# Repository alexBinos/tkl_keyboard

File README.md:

# tkl_keyboard

A custom tenkeyless keyboard with extra hardware features including;

- ATMEGA32U4 microcontroller compatible with QMK firmware
- 2x optional rotary encoders
- I2C breakout to support an OLED display
- Per-key RGB LED lighting and underglow lighting
- Hot-swap key switch sockets
- 4 port USB 2.0 HUB with 3 spare downstream ports
- Optional external power circuit supplying up to 2A for USB downstream and onboard power requirements

<br>

See `Firmware/` for example QMK projects. Note that some pin assignments changed between v0 and v1, see `Documents/tkl_keyboard v1 changes.md`. Pre-built binaries for the default configurations are also provided in `Firmware/bin`.

<br>

There are two versions of the case, both are compatible with hardware v0 and v1. The v1 case is a more integrated design, easier to assemble and can be positioned at a number of different angles.

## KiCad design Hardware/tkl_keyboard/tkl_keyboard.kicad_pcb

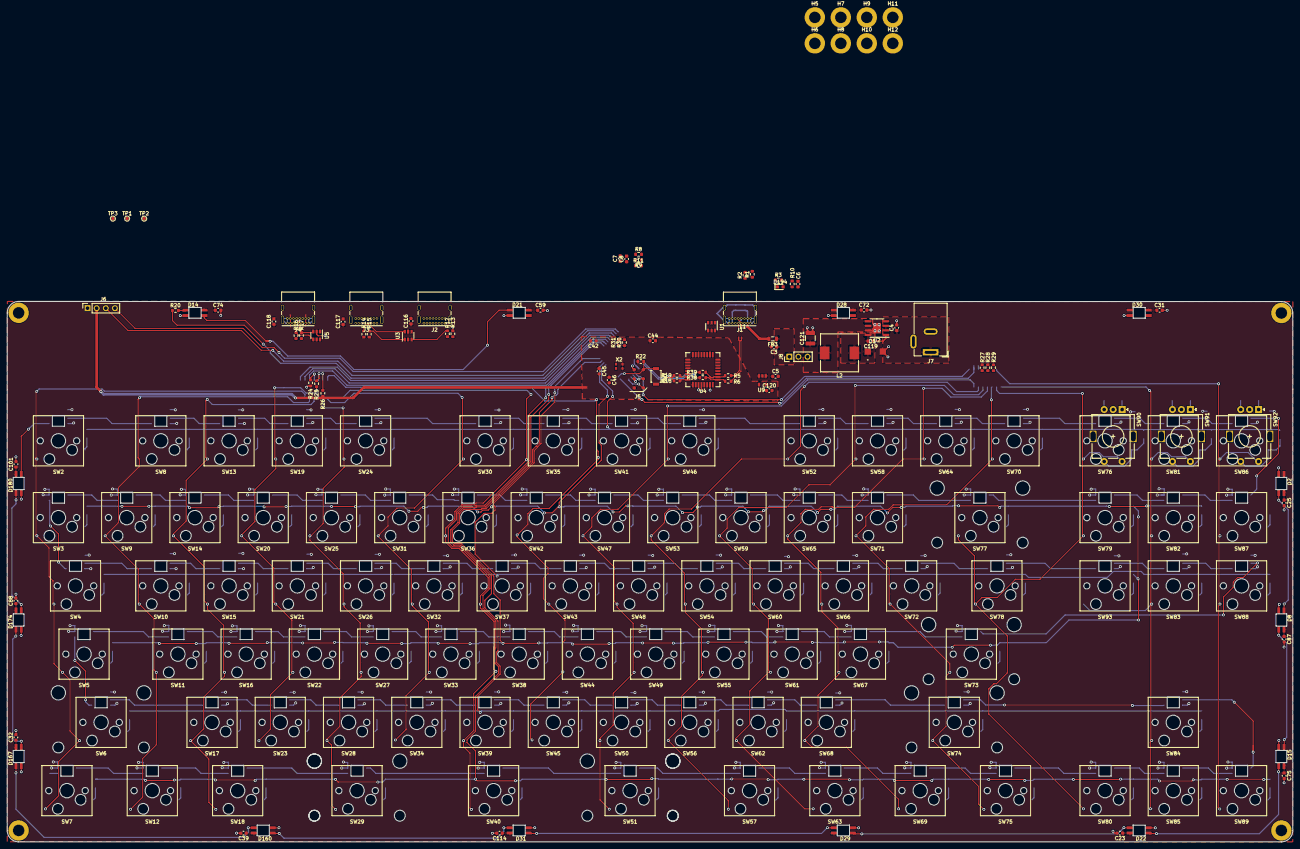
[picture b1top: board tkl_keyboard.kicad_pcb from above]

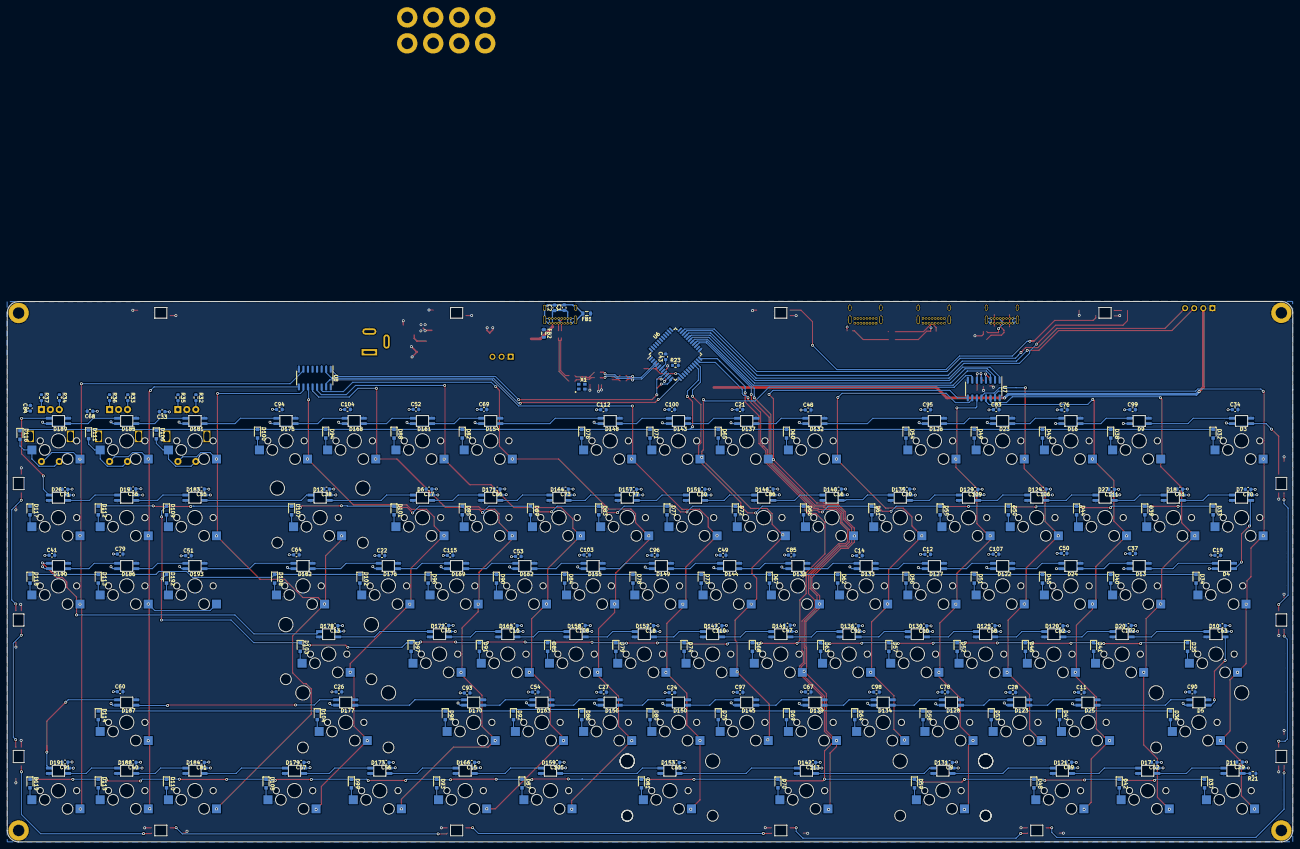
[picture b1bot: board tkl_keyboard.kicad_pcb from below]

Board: 2 copper layers, 358.8 x 150.8 mm, 484 parts (209 on the bottom side), 283 nets.

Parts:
C1, C4: 10uF; C_0603_1608Metric
C2, C6, C7, C43, C46, C116, C117, C118, C120: 1uF; C_0603_1608Metric
C3, C5, C8, C9, C10, C11, C12, C13, C14, C15, C16, C17, C18, C19, C20, C21, C22, C23, C24, C25, C26, C27, C28, C29, C30, C31, C32, C33, C34, C35, C36, C37, C38, C39, C40, C41, C42, C44, C45, C47, C48, C49, C50, C51, C52, C53, C54, C55, C56, C57, C58, C59, C60, C61, C62, C63, C64, C65, C66, C67, C68, C69, C70, C71, C72, C73, C74, C75, C76, C77, C78, C79, C80, C81, C82, C83, C84, C85, C86, C87, C88, C89, C90, C91, C92, C93, C94, C95, C96, C97, C98, C99, C100, C101, C102, C103, C104, C105, C106, C107, C108, C109, C110, C111, C112, C113, C114, C115, C119: 100nF; C_0603_1608Metric
C121: 47uF; C_1210_3225Metric
D1: D; DO-214AC
D2: UG_4; SK6812-MINI-E
D3: K0; SK6812-MINI-E
D4: K32; SK6812-MINI-E
D5: K63; SK6812-MINI-E
D6: K28; SK6812-MINI-E
D7: K16; SK6812-MINI-E
D8: UG_5; SK6812-MINI-E
D9: K1; SK6812-MINI-E
D10: K48; SK6812-MINI-E
D11: K77; SK6812-MINI-E
D12: K29; SK6812-MINI-E
D13: K33; SK6812-MINI-E
D14: UG_0; SK6812-MINI-E
D15: UG_6; SK6812-MINI-E
D16: K2; SK6812-MINI-E
D17: K64; SK6812-MINI-E
D18: K17; SK6812-MINI-E
D19: K30; SK6812-MINI-E
D20: K49; SK6812-MINI-E
D21: UG_1; SK6812-MINI-E
D22: UG_7; SK6812-MINI-E
D23: K3; SK6812-MINI-E
D24: K34; SK6812-MINI-E
D25: K65; SK6812-MINI-E
D26: K31; SK6812-MINI-E
D27: K18; SK6812-MINI-E
D28: UG_2; SK6812-MINI-E
D29: UG_8; SK6812-MINI-E
D30: UG_3; SK6812-MINI-E
D31: UG_9; SK6812-MINI-E
D32, D33, D34, D35, D36, D37, D38, D39, D40, D41, D42, D43, D44, D45, D46, D47, D48, D49, D50, D51, D52, D53, D54, D55, D56, D57, D58, D59, D60, D61, D62, D63, D64, D65, D66, D67, D68, D69, D70, D71, D72, D73, D74, D75, D76, D77, D78, D79, D80, D81, D82, D83, D84, D85, D86, D87, D88, D89, D90, D91, D92, D93, D94, D95, D96, D97, D98, D99, D100, D101, D102, D103, D104, D105, D106, D107, D108, D109, D110, D111, D112, D113, D114, D115, D116, D117, D118, D119, D192: D; SOD323_HS
D120: K50; SK6812-MINI-E
D121: K78; SK6812-MINI-E
D122: K35; SK6812-MINI-E
D123: K66; SK6812-MINI-E
D124: K19; SK6812-MINI-E
D125: K51; SK6812-MINI-E
D126: K4; SK6812-MINI-E
D127: K36; SK6812-MINI-E
D128: K67; SK6812-MINI-E
D129: K20; SK6812-MINI-E
D130: K52; SK6812-MINI-E
D131: K79; SK6812-MINI-E
D132: K5; SK6812-MINI-E
D133: K37; SK6812-MINI-E
D134: K68; SK6812-MINI-E
D135: K21; SK6812-MINI-E
D136: K53; SK6812-MINI-E
D137: K6; SK6812-MINI-E
D138: K38; SK6812-MINI-E
D139: K69; SK6812-MINI-E
D140: K22; SK6812-MINI-E
D141: K54; SK6812-MINI-E
D142: K80; SK6812-MINI-E
D143: K7; SK6812-MINI-E
D144: K39; SK6812-MINI-E
D145: K70; SK6812-MINI-E
D146: K23; SK6812-MINI-E
D147: K55; SK6812-MINI-E
D148: K8; SK6812-MINI-E
D149: K40; SK6812-MINI-E
D150: K71; SK6812-MINI-E
D151: K24; SK6812-MINI-E
D152: K56; SK6812-MINI-E
D153: K81; SK6812-MINI-E
D154: K9; SK6812-MINI-E
D155: K41; SK6812-MINI-E
D156: K72; SK6812-MINI-E
D157: K25; SK6812-MINI-E
D158: K57; SK6812-MINI-E
D159: K82; SK6812-MINI-E
D160: UG_10; SK6812-MINI-E
D161: K10; SK6812-MINI-E
D162: K42; SK6812-MINI-E
D163: K73; SK6812-MINI-E
D164: K26; SK6812-MINI-E
D165: K58; SK6812-MINI-E
D166: K83; SK6812-MINI-E
D167: UG_11; SK6812-MINI-E
D168: K11; SK6812-MINI-E
D169: K43; SK6812-MINI-E
D170: K74; SK6812-MINI-E
D171: K27; SK6812-MINI-E
D172: K59; SK6812-MINI-E
D173: K84; SK6812-MINI-E
D174: UG_12; SK6812-MINI-E
D175: K12; SK6812-MINI-E
D176: K44; SK6812-MINI-E
D177: K75; SK6812-MINI-E
D178: K60; SK6812-MINI-E
D179: K85; SK6812-MINI-E
D180: UG_13; SK6812-MINI-E
D181: K13; SK6812-MINI-E
D182: K45; SK6812-MINI-E
D183: K61; SK6812-MINI-E
D184: K86; SK6812-MINI-E
D185: K14; SK6812-MINI-E
D186: K46; SK6812-MINI-E
D187: K76; SK6812-MINI-E
D188: K87; SK6812-MINI-E
D189: K15; SK6812-MINI-E
D190: K47; SK6812-MINI-E
D191: K88; SK6812-MINI-E
D193: K62; SK6812-MINI-E
D194: LED; D_0603_1608Metric
FB1, FB2, FB3: Ferrite_Bead; L_0805_2012Metric
H1, H2, H3, H4, H5, H6, H7, H8, H9, H10, H11, H12: MountingHole_Pad; MountingHole_3.2mm_M3_ISO7380_Pad
J1, J2, J3, J4: USB_C_Receptacle_USB2.0; USB_C_Receptacle_GCT_USB4085
J5: Conn_02x03_Odd_Even; ISP_POGO
J6: Conn_01x04_Female; OLED_128_64
J7: Barrel_Jack_MountingPin; BarrelJack_Wuerth_6941xx301002
J8: Conn_01x03_Male; PinHeader_1x03_P2.54mm_Vertical
L1: L_Core_Iron_Coupled_1423; SMM2012E
L2: L; L_10.4x10.4_H4.8
R1, R2: 5K1; R_0603_1608Metric
R3: 330R; R_0603_1608Metric
R5, R6, R12, R13, R14, R15, R16, R17, R18, R19: 22R; R_0603_1608Metric
R8, R9, R22, R23, R24, R25, R26, R27, R28, R29, R32, R33, R34, R35, R36, R37: 10K; R_0603_1608Metric
R10, R11, R30, R31: 4K7; R_0603_1608Metric
R20, R21: Rt; R_0603_1608Metric
R38, R39: OPT; R_0603_1608Metric
SW1: SW_Push; SW_SPST_B3U-1000P
SW2: K0; CherryMX_1.00u_PCB_KailhSocket
SW3: K16; CherryMX_1.00u_PCB_KailhSocket
SW4: K32; CherryMX_1.50u_PCB_KailhSocket
SW5: K48; CherryMX_1.75u_PCB_KailhSocket
SW6: K63; CherryMX_2.25u_PCB_KailhSocket_StabWireBottom
SW7: K77; CherryMX_1.25u_PCB_KailhSocket
SW8: K1; CherryMX_1.00u_PCB_KailhSocket
SW9: K17; CherryMX_1.00u_PCB_KailhSocket
SW10: K33; CherryMX_1.00u_PCB_KailhSocket
SW11: K49; CherryMX_1.00u_PCB_KailhSocket
SW12: K64; CherryMX_1.25u_PCB_KailhSocket
SW13: K2; CherryMX_1.00u_PCB_KailhSocket
SW14: K18; CherryMX_1.00u_PCB_KailhSocket
SW15: K34; CherryMX_1.00u_PCB_KailhSocket
SW16: K50; CherryMX_1.00u_PCB_KailhSocket
SW17: K65; CherryMX_1.00u_PCB_KailhSocket
SW18: K78; CherryMX_1.25u_PCB_KailhSocket
SW19: K3; CherryMX_1.00u_PCB_KailhSocket
SW20: K19; CherryMX_1.00u_PCB_KailhSocket
SW21: K35; CherryMX_1.00u_PCB_KailhSocket
SW22: K51; CherryMX_1.00u_PCB_KailhSocket
SW23: K66; CherryMX_1.00u_PCB_KailhSocket
SW24: K4; CherryMX_1.00u_PCB_KailhSocket
SW25: K20; CherryMX_1.00u_PCB_KailhSocket
SW26: K36; CherryMX_1.00u_PCB_KailhSocket
SW27: K52; CherryMX_1.00u_PCB_KailhSocket
SW28: K67; CherryMX_1.00u_PCB_KailhSocket
SW29: K79; CherryMX_2.25u_PCB_KailhSocket_StabWireBottom
SW30: K5; CherryMX_1.00u_PCB_KailhSocket
SW31: K21; CherryMX_1.00u_PCB_KailhSocket
SW32: K37; CherryMX_1.00u_PCB_KailhSocket
SW33: K53; CherryMX_1.00u_PCB_KailhSocket
SW34: K68; CherryMX_1.00u_PCB_KailhSocket
SW35: K6; CherryMX_1.00u_PCB_KailhSocket
SW36: K22; CherryMX_1.00u_PCB_KailhSocket
SW37: K38; CherryMX_1.00u_PCB_KailhSocket
SW38: K54; CherryMX_1.00u_PCB_KailhSocket
SW39: K69; CherryMX_1.00u_PCB_KailhSocket
SW40: K80; CherryMX_6.25u_PCB_KailhSocket_StabWireBottom
SW41: K7; CherryMX_1.00u_PCB_KailhSocket
SW42: K23; CherryMX_1.00u_PCB_KailhSocket
SW43: K39; CherryMX_1.00u_PCB_KailhSocket
SW44: K55; CherryMX_1.00u_PCB_KailhSocket
SW45: K70; CherryMX_1.00u_PCB_KailhSocket
SW46: K8; CherryMX_1.00u_PCB_KailhSocket
SW47: K24; CherryMX_1.00u_PCB_KailhSocket
SW48: K40; CherryMX_1.00u_PCB_KailhSocket
SW49: K56; CherryMX_1.00u_PCB_KailhSocket
SW50: K71; CherryMX_1.00u_PCB_KailhSocket
SW51: K81; CherryMX_2.25u_PCB_KailhSocket_StabWireBottom
SW52: K9; CherryMX_1.00u_PCB_KailhSocket
SW53: K25; CherryMX_1.00u_PCB_KailhSocket
SW54: K41; CherryMX_1.00u_PCB_KailhSocket
SW55: K57; CherryMX_1.00u_PCB_KailhSocket
SW56: K72; CherryMX_1.00u_PCB_KailhSocket
SW57: K82; CherryMX_1.25u_PCB_KailhSocket
SW58: K10; CherryMX_1.00u_PCB_KailhSocket
SW59: K26; CherryMX_1.00u_PCB_KailhSocket
SW60: K42; CherryMX_1.00u_PCB_KailhSocket
SW61: K58; CherryMX_1.00u_PCB_KailhSocket
SW62: K73; CherryMX_1.00u_PCB_KailhSocket
SW63: K83; CherryMX_1.25u_PCB_KailhSocket
SW64: K11; CherryMX_1.00u_PCB_KailhSocket
SW65: K27; CherryMX_1.00u_PCB_KailhSocket
SW66: K43; CherryMX_1.00u_PCB_KailhSocket
SW67: K59; CherryMX_1.00u_PCB_KailhSocket
SW68: K74; CherryMX_1.00u_PCB_KailhSocket
SW69: K84; CherryMX_1.25u_PCB_KailhSocket
SW70: K12; CherryMX_1.00u_PCB_KailhSocket
SW71: K28; CherryMX_1.00u_PCB_KailhSocket
SW72: K44; CherryMX_1.00u_PCB_KailhSocket
SW73: K60; CherryMX_2.25u_PCB_KailhSocket_StabWireBottom
SW74: K75; CherryMX_2.75u_PCB_KailhSocket_StabWireBottom
SW75: K85; CherryMX_1.25u_PCB_KailhSocket
SW76: K13; CherryMX_1.00u_PCB_KailhSocket
SW77: K29; CherryMX_2.00u_PCB_KailhSocket_StabWireBottom
SW78: K45; CherryMX_1.50u_PCB_KailhSocket
SW79: K61; CherryMX_1.00u_PCB_KailhSocket
SW80: K86; CherryMX_1.00u_PCB_KailhSocket
SW81: K14; CherryMX_1.00u_PCB_KailhSocket
SW82: K30; CherryMX_1.00u_PCB_KailhSocket
SW83: K46; CherryMX_1.00u_PCB_KailhSocket
SW84: K76; CherryMX_1.00u_PCB_KailhSocket
SW85: K87; CherryMX_1.00u_PCB_KailhSocket
SW86: K15; CherryMX_1.00u_PCB_KailhSocket
SW87: K31; CherryMX_1.00u_PCB_KailhSocket
SW88: K47; CherryMX_1.00u_PCB_KailhSocket
SW89: K88; CherryMX_1.00u_PCB_KailhSocket
SW90, SW91, SW92: Rotary_Encoder_Switch; RotaryEncoder_Alps_EC11E-Switch_Vertical_H20mm
SW93: K62; CherryMX_1.00u_PCB_KailhSocket
TP1, TP2, TP3: TestPoint; TestPoint_Pad_D1.0mm
U1, U3, U5: SRV05-4; SOT-23-6
U2: ADP2303ARDZ-5.0; SOIC-8-1EP_3.9x4.9mm_P1.27mm_EP2.29x3mm
U4: TUSB2046b
U6: ATmega32U4-AU; TQFP-44_10x10mm_P0.8mm
U7, U8: CD74HC238; SOIC-16_3.9x9.9mm_P1.27mm
U9: TCR2EF33; TCR2EF33_SOT25
X1: 625L3C006M00000
X2: KC2016K

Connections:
+3V3: C7.1, C8.1, C42.1, C44.1, C45.1, C46.1, C120.1, D194.2, J5.2, J6.2, R8.2, R10.2, R11.2, R22.1, R26.2, R29.2, R30.1, R31.1, R32.1, R33.1, R34.1, R35.1, R36.1, R37.1, TP2.1, U4.3, U4.10, U4.14, U4.18, U4.22, U4.25, U6.2, U6.14, U6.24, U6.34, U6.42, U6.44, U7.16, U8.16, U9.5, X1.1, X1.4, X2.1, X2.4
+5V: C5.1, C9.1, C10.1, C11.1, C12.1, C13.1, C14.1, C15.1, C16.1, C17.1, C18.1, C19.1, C20.1, C21.1, C22.1, C23.1, C24.1, C25.1, C26.1, C27.1, C28.1, C29.1, C30.1, C31.1, C32.1, C33.1, C34.1, C35.1, C36.1, C37.1, C38.1, C39.1, C40.1, C41.1, C47.1, C48.1, C49.1, C50.1, C51.1, C52.1, C53.1, C54.1, C55.1, C56.1, C57.1, C58.1, C59.1, C60.1, C61.1, C62.1, C63.1, C64.1, C65.1, C66.1, C67.1, C68.1, C69.1, C70.1, C71.1, C72.1, C73.1, C74.1, C75.1, C76.1, C77.1, C78.1, C79.1, C80.1, C81.1, C82.1, C83.1, C84.1, C85.1, C86.1, C87.1, C88.1, C89.1, C90.1, C91.1, C92.1, C93.1, C94.1, C95.1, C96.1, C97.1, C98.1, C99.1, C100.1, C101.1, C102.1, C103.1, C104.1, C105.1, C106.1, C107.1, C108.1, C109.1, C110.1, C111.1, C112.1, C113.1, C114.1, C115.1, C116.1, C117.1, C118.1, D2.1, D3.1, D4.1, D5.1, D6.1, D7.1, D8.1, D9.1, D10.1, D11.1, D12.1, D13.1, D14.1, D15.1, D16.1, D17.1, D18.1, D19.1, D20.1, D21.1, D22.1, D23.1, D24.1, D25.1, D26.1, D27.1, D28.1, D29.1, D30.1, D31.1, D120.1, D121.1, D122.1, D123.1, D124.1, D125.1, D126.1, D127.1, D128.1, D129.1, D130.1, D131.1, D132.1, D133.1, D134.1, D135.1, D136.1, D137.1, D138.1, D139.1, D140.1, D141.1, D142.1, D143.1, D144.1, D145.1, D146.1, D147.1, D148.1, D149.1, D150.1, D151.1, D152.1, D153.1, D154.1, D155.1, D156.1, D157.1, D158.1, D159.1, D160.1, D161.1, D162.1, D163.1, D164.1, D165.1, D166.1, D167.1, D168.1, D169.1, D170.1, D171.1, D172.1, D173.1, D174.1, D175.1, D176.1, D177.1, D178.1, D179.1, D180.1, D181.1, D182.1, D183.1, D184.1, D185.1, D186.1, D187.1, D188.1, D189.1, D190.1, D191.1, D193.1, J2.A4, J2.A9, J2.B4, J2.B9, J3.A4, J3.A9, J3.B4, J3.B9, J4.A4, J4.A9, J4.B4, J4.B9, J8.2, TP3.1, U3.5, U5.5, U9.1, U9.3
+5V0_EXT: C121.1, J8.3, L2.2, U2.5
+5V0_USB: C3.1, FB3.1, J8.1
/Column Decoder/COLA[0]: U6.29, U7.1
/Column Decoder/COLA[1]: U6.28, U7.2
/Column Decoder/COLA[2]: U6.27, U7.3
/Column Decoder/COLA[3]: U6.8, U8.1
/Column Decoder/COLA[4]: U6.12, U8.2
/Column Decoder/COLA[5]: U6.1, U8.3
/Column Decoder/COL[0]: SW2.2, SW3.2, SW4.2, SW5.2, SW6.2, SW7.2, U7.15
/Column Decoder/COL[1]: SW8.2, SW9.2, SW10.2, SW11.2, SW12.2, U7.14
/Column Decoder/COL[2]: SW13.2, SW14.2, SW15.2, SW16.2, SW17.2, SW18.2, U7.13
/Column Decoder/COL[3]: SW19.2, SW20.2, SW21.2, SW22.2, SW23.2, U7.12
/Column Decoder/COL[4]: SW24.2, SW25.2, SW26.2, SW27.2, SW28.2, SW29.2, U7.11
/Column Decoder/COL[5]: SW30.2, SW31.2, SW32.2, SW33.2, SW34.2, U7.10
/Column Decoder/COL[6]: SW35.2, SW36.2, SW37.2, SW38.2, SW39.2, SW40.2, U7.9
/Column Decoder/COL[7]: SW41.2, SW42.2, SW43.2, SW44.2, SW45.2, U7.7
/Column Decoder/COL[8]: SW46.2, SW47.2, SW48.2, SW49.2, SW50.2, SW51.2, U8.15
/Column Decoder/COL[9]: SW52.2, SW53.2, SW54.2, SW55.2, SW56.2, SW57.2, U8.14
/Column Decoder/COL[10]: SW58.2, SW59.2, SW60.2, SW61.2, SW62.2, SW63.2, U8.13
/Column Decoder/COL[11]: SW64.2, SW65.2, SW66.2, SW67.2, SW68.2, SW69.2, U8.12
/Column Decoder/COL[12]: SW70.2, SW71.2, SW72.2, SW73.2, SW74.2, SW75.2, U8.11
/Misc/ENC_A[0]: R35.2, SW90.A, U6.41
/Misc/ENC_A[1]: R36.2, SW91.A, U6.39
/Misc/ENC_A[2]: R37.2, SW92.A, U6.37
/Misc/ENC_B[0]: R32.2, SW90.B, U6.40
/Misc/ENC_B[1]: R33.2, SW91.B, U6.38
/Misc/ENC_B[2]: R34.2, SW92.B, U6.36
/Misc/SCL: J6.4, R30.2, U6.32
/Misc/SDA: J6.3, R31.2, U6.31
/Power/DCDC_IN: C4.1, J7.1, U2.2, U2.3
/Power/SW: C119.2, D1.1, L2.1, U2.8
/Switches/ROW[0]: D32.1, D38.1, D43.1, D49.1, D54.1, D60.1, D65.1, D71.1, D76.1, D82.1, D88.1, D94.1, D100.1, D106.1, D111.1, D116.1, U6.19
/Switches/ROW[1]: D33.1, D39.1, D44.1, D50.1, D55.1, D61.1, D66.1, D72.1, D77.1, D83.1, D89.1, D95.1, D101.1, D107.1, D112.1, D117.1, U6.20
/Switches/ROW[2]: D34.1, D40.1, D45.1, D51.1, D56.1, D62.1, D67.1, D73.1, D78.1, D84.1, D90.1, D96.1, D102.1, D108.1, D113.1, D118.1, U6.22
/Switches/ROW[3]: D35.1, D41.1, D46.1, D52.1, D57.1, D63.1, D68.1, D74.1, D79.1, D85.1, D91.1, D97.1, D103.1, D109.1, D192.1, U6.21
/Switches/ROW[4]: D36.1, D47.1, D53.1, D58.1, D64.1, D69.1, D75.1, D80.1, D86.1, D92.1, D98.1, D104.1, D114.1, U6.25
/Switches/ROW[5]: D37.1, D42.1, D48.1, D59.1, D70.1, D81.1, D87.1, D93.1, D99.1, D105.1, D110.1, D115.1, D119.1, U6.26
/USB Downstream 0/USBD+: J2.A6, J2.B6, R12.1, U3.3
/USB Downstream 0/USBD-: J2.A7, J2.B7, R13.1, U3.4
/USB Downstream 1/USBD+: J3.A6, J3.B6, R14.1, U3.6
/USB Downstream 1/USBD-: J3.A7, J3.B7, R15.1, U3.1
/USB Downstream 2/USBD+: J4.A6, J4.B6, R16.1, U5.4
/USB Downstream 2/USBD-: J4.A7, J4.B7, R17.1, U5.3
/USB HUB/D1+: R12.2, U4.12
/USB HUB/D1-: R13.2, U4.11
/USB HUB/D2+: R14.2, U4.16
/USB HUB/D2-: R15.2, U4.15
/USB HUB/D3+: R16.2, U4.20
/USB HUB/D3-: R17.2, U4.19
/USB HUB/D4+: R18.2, U4.24
/USB HUB/D4-: R19.2, U4.23
/USB HUB/USB_DOWNSTREAM_LOCAL_OUT+: R18.1, R38.1, U6.4
/USB HUB/USB_DOWNSTREAM_LOCAL_OUT-: R19.1, R39.1, U6.3
/USB HUB/USB_UPSTREAM_IN+: R6.1, R38.2, U4.1
/USB HUB/USB_UPSTREAM_IN-: R5.1, R39.2, U4.2
/USB Upstream/CD+: J1.A6, J1.B6, L1.3, U1.1
/USB Upstream/CD-: J1.A7, J1.B7, L1.4, U1.6
/USB Upstream/D+: L1.2, R6.2
/USB Upstream/D-: L1.1, R5.2
/uController/RGB_DOUT: R20.1, U6.30
ENC_COL[0]: SW76.2, SW77.2, SW78.2, SW79.2, SW80.2, SW90.S2, U8.10
ENC_COL[1]: SW81.2, SW82.2, SW83.2, SW84.2, SW85.2, SW91.S2, SW93.2, U8.9
ENC_COL[2]: SW86.2, SW87.2, SW88.2, SW89.2, SW92.S2, U8.7
ENC_ROW[0]: D106.2, SW76.1, SW90.S1
ENC_ROW[1]: D111.2, SW81.1, SW91.S1
ENC_ROW[2]: D116.2, SW86.1, SW92.S1
GND: C3.2, C4.2, C5.2, C6.1, C7.2, C8.2, C9.2, C10.2, C11.2, C12.2, C13.2, C14.2, C15.2, C16.2, C17.2, C18.2, C19.2, C20.2, C21.2, C22.2, C23.2, C24.2, C25.2, C26.2, C27.2, C28.2, C29.2, C30.2, C31.2, C32.2, C33.2, C34.2, C35.2, C36.2, C37.2, C38.2, C39.2, C40.2, C41.2, C42.2, C43.2, C44.2, C45.2, C46.2, C47.2, C48.2, C49.2, C50.2, C51.2, C52.2, C53.2, C54.2, C55.2, C56.2, C57.2, C58.2, C59.2, C60.2, C61.2, C62.2, C63.2, C64.2, C65.2, C66.2, C67.2, C68.2, C69.2, C70.2, C71.2, C72.2, C73.2, C74.2, C75.2, C76.2, C77.2, C78.2, C79.2, C80.2, C81.2, C82.2, C83.2, C84.2, C85.2, C86.2, C87.2, C88.2, C89.2, C90.2, C91.2, C92.2, C93.2, C94.2, C95.2, C96.2, C97.2, C98.2, C99.2, C100.2, C101.2, C102.2, C103.2, C104.2, C105.2, C106.2, C107.2, C108.2, C109.2, C110.2, C111.2, C112.2, C113.2, C114.2, C115.2, C116.2, C117.2, C118.2, C120.2, C121.2, D1.2, D2.3, D3.3, D4.3, D5.3, D6.3, D7.3, D8.3, D9.3, D10.3, D11.3, D12.3, D13.3, D14.3, D15.3, D16.3, D17.3, D18.3, D19.3, D20.3, D21.3, D22.3, D23.3, D24.3, D25.3, D26.3, D27.3, D28.3, D29.3, D30.3, D31.3, D120.3, D121.3, D122.3, D123.3, D124.3, D125.3, D126.3, D127.3, D128.3, D129.3, D130.3, D131.3, D132.3, D133.3, D134.3, D135.3, D136.3, D137.3, D138.3, D139.3, D140.3, D141.3, D142.3, D143.3, D144.3, D145.3, D146.3, D147.3, D148.3, D149.3, D150.3, D151.3, D152.3, D153.3, D154.3, D155.3, D156.3, D157.3, D158.3, D159.3, D160.3, D161.3, D162.3, D163.3, D164.3, D165.3, D166.3, D167.3, D168.3, D169.3, D170.3, D171.3, D172.3, D173.3, D174.3, D175.3, D176.3, D177.3, D178.3, D179.3, D180.3, D181.3, D182.3, D183.3, D184.3, D185.3, D186.3, D187.3, D188.3, D189.3, D190.3, D191.3, D193.3, FB1.1, FB2.1, H1.1, H2.1, H3.1, H4.1, H5.1, H6.1, H7.1, H8.1, H9.1, H10.1, H11.1, H12.1, J2.A1, J2.A12, J2.B1, J2.B12, J2.S1, J3.A1, J3.A12, J3.B1, J3.B12, J3.S1, J4.A1, J4.A12, J4.B1, J4.B12, J4.S1, J5.6, J6.1, J7.2, R1.1, R2.1, R3.1, R9.1, R21.1, R23.2, R24.2, R25.2, R27.2, R28.2, SW1.2, SW90.C, SW91.C, SW92.C, TP1.1, U1.2, U2.7, U2.9, U3.2, U4.7, U4.27, U4.28, U4.31, U5.2, U6.5, U6.15, U6.23, U6.35, U6.43, U7.8, U8.8, U9.2, X1.2, X2.2
MISO: J5.1, U6.11
MOSI: J5.4, U6.10
unnamed: C1.2, C2.2, FB1.2, FB2.2, J1.A1, J1.A12, J1.B1, J1.B12, J1.S1
unnamed: C6.2, R10.1, U4.4
unnamed: C43.1, U6.6
unnamed: C119.1, U2.1
unnamed: D2.2, D8.4
unnamed: D2.4, D30.2
unnamed: D3.2, D9.4
unnamed: D4.4, D7.2
unnamed: D5.4, D10.2
unnamed: D10.4, D20.2
unnamed: D11.2, R21.2
unnamed: D11.4, D17.2
unnamed: D6.4, D12.2
unnamed: D12.4, D183.2
unnamed: D13.2, D24.4
unnamed: D4.2, D13.4
unnamed: D14.2, D21.4
unnamed: D14.4, R20.2
unnamed: D15.2, D22.4
unnamed: D8.2, D15.4
unnamed: D16.2, D23.4
unnamed: D9.2, D16.4
unnamed: D7.4, D18.2
unnamed: D18.4, D27.2
unnamed: D19.4, D26.2
unnamed: D21.2, D28.4
unnamed: D22.2, D29.4
unnamed: D5.2, D25.4
unnamed: D28.2, D30.4
unnamed: D29.2, D31.4
unnamed: D32.2, SW2.1
unnamed: D33.2, SW3.1
unnamed: D34.2, SW4.1
unnamed: D35.2, SW5.1
unnamed: D36.2, SW6.1
unnamed: D37.2, SW7.1
unnamed: D38.2, SW8.1
unnamed: D39.2, SW9.1
unnamed: D40.2, SW10.1
unnamed: D41.2, SW11.1
unnamed: D42.2, SW12.1
unnamed: D43.2, SW13.1
unnamed: D44.2, SW14.1
unnamed: D45.2, SW15.1
unnamed: D46.2, SW16.1
unnamed: D47.2, SW17.1
unnamed: D48.2, SW18.1
unnamed: D49.2, SW19.1
unnamed: D50.2, SW20.1
unnamed: D51.2, SW21.1
unnamed: D52.2, SW22.1
unnamed: D53.2, SW23.1
unnamed: D54.2, SW24.1
unnamed: D55.2, SW25.1
unnamed: D56.2, SW26.1
unnamed: D57.2, SW27.1
unnamed: D58.2, SW28.1
unnamed: D59.2, SW29.1
unnamed: D60.2, SW30.1
unnamed: D61.2, SW31.1
unnamed: D62.2, SW32.1
unnamed: D63.2, SW33.1
unnamed: D64.2, SW34.1
unnamed: D65.2, SW35.1
unnamed: D66.2, SW36.1
unnamed: D67.2, SW37.1
unnamed: D68.2, SW38.1
unnamed: D69.2, SW39.1
unnamed: D70.2, SW40.1
unnamed: D71.2, SW41.1
unnamed: D72.2, SW42.1
unnamed: D73.2, SW43.1
unnamed: D74.2, SW44.1
unnamed: D75.2, SW45.1
unnamed: D76.2, SW46.1
unnamed: D77.2, SW47.1
unnamed: D78.2, SW48.1
unnamed: D79.2, SW49.1
unnamed: D80.2, SW50.1
unnamed: D81.2, SW51.1
unnamed: D82.2, SW52.1
unnamed: D83.2, SW53.1
unnamed: D84.2, SW54.1
unnamed: D85.2, SW55.1
unnamed: D86.2, SW56.1
unnamed: D87.2, SW57.1
unnamed: D88.2, SW58.1
unnamed: D89.2, SW59.1
unnamed: D90.2, SW60.1
unnamed: D91.2, SW61.1
unnamed: D92.2, SW62.1
unnamed: D93.2, SW63.1
unnamed: D94.2, SW64.1
unnamed: D95.2, SW65.1
unnamed: D96.2, SW66.1
unnamed: D97.2, SW67.1
unnamed: D98.2, SW68.1
unnamed: D99.2, SW69.1
unnamed: D100.2, SW70.1
unnamed: D101.2, SW71.1
unnamed: D102.2, SW72.1
unnamed: D103.2, SW73.1
unnamed: D104.2, SW74.1
unnamed: D105.2, SW75.1
unnamed: D107.2, SW77.1
unnamed: D108.2, SW78.1
unnamed: D109.2, SW79.1
unnamed: D110.2, SW80.1
unnamed: D112.2, SW82.1
unnamed: D113.2, SW83.1
unnamed: D114.2, SW84.1
unnamed: D115.2, SW85.1
unnamed: D117.2, SW87.1
unnamed: D118.2, SW88.1
unnamed: D119.2, SW89.1
unnamed: D20.4, D120.2
unnamed: D120.4, D125.2
unnamed: D17.4, D121.2
unnamed: D121.4, D131.2
unnamed: D122.2, D127.4
unnamed: D24.2, D122.4
unnamed: D123.2, D128.4
unnamed: D25.2, D123.4
unnamed: D27.4, D124.2
unnamed: D124.4, D129.2
unnamed: D125.4, D130.2
unnamed: D126.2, D132.4
unnamed: D23.2, D126.4
unnamed: D127.2, D133.4
unnamed: D128.2, D134.4
unnamed: D129.4, D135.2
unnamed: D130.4, D136.2
unnamed: D131.4, D142.2
unnamed: D132.2, D137.4
unnamed: D133.2, D138.4
unnamed: D134.2, D139.4
unnamed: D135.4, D140.2
unnamed: D136.4, D141.2
unnamed: D137.2, D143.4
unnamed: D138.2, D144.4
unnamed: D139.2, D145.4
unnamed: D140.4, D146.2
unnamed: D141.4, D147.2
unnamed: D142.4, D153.2
unnamed: D143.2, D148.4
unnamed: D144.2, D149.4
unnamed: D145.2, D150.4
unnamed: D146.4, D151.2
unnamed: D147.4, D152.2
unnamed: D148.2, D154.4
unnamed: D149.2, D155.4
unnamed: D150.2, D156.4
unnamed: D151.4, D157.2
unnamed: D152.4, D158.2
unnamed: D153.4, D159.2
unnamed: D154.2, D161.4
unnamed: D155.2, D162.4
unnamed: D156.2, D163.4
unnamed: D157.4, D164.2
unnamed: D158.4, D165.2
unnamed: D159.4, D166.2
unnamed: D160.2, D167.4
unnamed: D31.2, D160.4
unnamed: D161.2, D168.4
unnamed: D162.2, D169.4
unnamed: D163.2, D170.4
unnamed: D164.4, D171.2
unnamed: D165.4, D172.2
unnamed: D166.4, D173.2
unnamed: D167.2, D174.4
unnamed: D168.2, D175.4
unnamed: D169.2, D176.4
unnamed: D170.2, D177.4
unnamed: D6.2, D171.4
unnamed: D172.4, D178.2
unnamed: D173.4, D179.2
unnamed: D174.2, D180.4
unnamed: D175.2, D181.4
unnamed: D176.2, D182.4
unnamed: D177.2, D187.4
unnamed: D178.4, D190.2
unnamed: D179.4, D184.2
unnamed: D181.2, D185.4
unnamed: D182.2, D193.4
unnamed: D19.2, D183.4
unnamed: D184.4, D188.2
unnamed: D185.2, D189.4
unnamed: D186.2, D190.4
unnamed: D186.4, D193.2
unnamed: D187.2, D191.4
unnamed: D188.4, D191.2
unnamed: D26.4, D189.2
unnamed: D192.2, SW93.1
unnamed: D194.1, R3.2
unnamed: J1.A5, R2.2
unnamed: J1.B5, R1.2
unnamed: R8.1, U4.26
unnamed: R9.2, U4.6
unnamed: R11.1, U4.8
unnamed: R23.1, U6.33
unnamed: R24.1, U7.4
unnamed: R25.1, U7.5
unnamed: R26.1, U7.6
unnamed: R27.1, U8.4
unnamed: R28.1, U8.5
unnamed: R29.1, U8.6
unnamed: U4.30, X1.3
unnamed: U6.17, X2.3
RST: J5.5, R22.2, SW1.1, U6.13
SCK: J5.3, U6.9
UG_OUT: D3.4, D180.2
VBUS: C1.1, C2.1, FB3.2, J1.A4, J1.A9, J1.B4, J1.B9, U1.5, U6.7

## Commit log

2021-08-25 schematic done
2021-08-26 Keyswitch, LED and diode placement done
2021-08-29 LEDs and diodes routed
2021-08-29 Switch matrix routed
2021-08-31 Rows and columns routed to controller. Extended top board edge to fit OLED. Removed optional resistors around CMC.
2021-09-04 Updating schematic
2021-09-07 Power supply routed
2021-09-07 First pass of routing done
2021-09-09 Fixing power/ground plane connections. Tidying some routing.
2021-09-12 Cleaning up silk layers, Adding pin 1 markers and text
2021-09-12 Added some missing capacitors, Fixed DC jack footprint connections
2021-09-12 Updating 3D file associations
2021-09-13 Updating gitignore
2021-09-13 Adding DXFs
2021-09-22 Fixing USB circuit, adding data line resistors as per AN-5052
2021-09-23 Changing diode direction: row to column
2021-09-23 Updating board with diode changes, rows routed
2021-09-24 Rows rerouted
2021-09-24 Tidying traces and silk, passing DRC
2021-09-24 Tidying schematic
2021-09-26 Generating gerbers
2021-10-06 Adding first pass of the firmware (untested)
2021-10-22 Updating firmware - works in hardware
2021-10-24 Adding working binary
2021-10-25 Removing debug code
2021-10-25 Working keymap
2022-05-21 Adding .zip and .rpt
2022-05-21 Removing redundant files
2022-05-21 Adding mechanical files
2022-05-21 Adding schematic pdf
2022-05-21 Hardware version 0
2022-05-21 Hardware version 1 initial commit
2022-05-21 Updating hardware versions
2022-05-21 Updating hardware design Moved I2C lines Routed line decoder enable lines Removed line decoder strap resistors Rounded corners on planes Disconnected mounting holes from ground
2022-08-08 v1 gerbers
2022-08-08 Generating v1 schematic
2022-08-08 Datasheets
2022-08-08 Updating v0 and v1 firmware
2022-08-08 binaries
2022-08-08 Adding change documents
2022-08-09 Updating DXFs
2022-08-09 v1 keyframe
2022-08-09 Edge cuts DXF
2022-08-09 v1 case and stand
2022-08-10 Updating README
2022-08-10 Scanning algorithm overview
2022-08-11 Increasing cut width between sections
2022-08-11 Moving v0 case files
2022-08-11 Moving v0 STEP
2022-10-15 Adding cutout for power selector jumper
2022-11-14 Adding encoder fix images
